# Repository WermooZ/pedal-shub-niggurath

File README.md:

# pedal-shub-niggurath

<br />This work is licensed under a <a rel="license" href="http://creativecommons.org/licenses/by-nc-sa/4.0/">Creative Commons Attribution-NonCommercial-ShareAlike 4.0 International License</a>.

Based on the **EQD Hoof** traced by **Kit Rae** at http://www.bigmuffpage.com/Big_Muff_Pi_versions_schematics_part4.html

Like original pedal it uses 2 germanium transistors on Q2 and Q3 however Q1 is changed to MSPA18 for bigger gain and has blend circuit.  

Thread on freestompboxes: https://www.freestompboxes.org/viewtopic.php?t=32611

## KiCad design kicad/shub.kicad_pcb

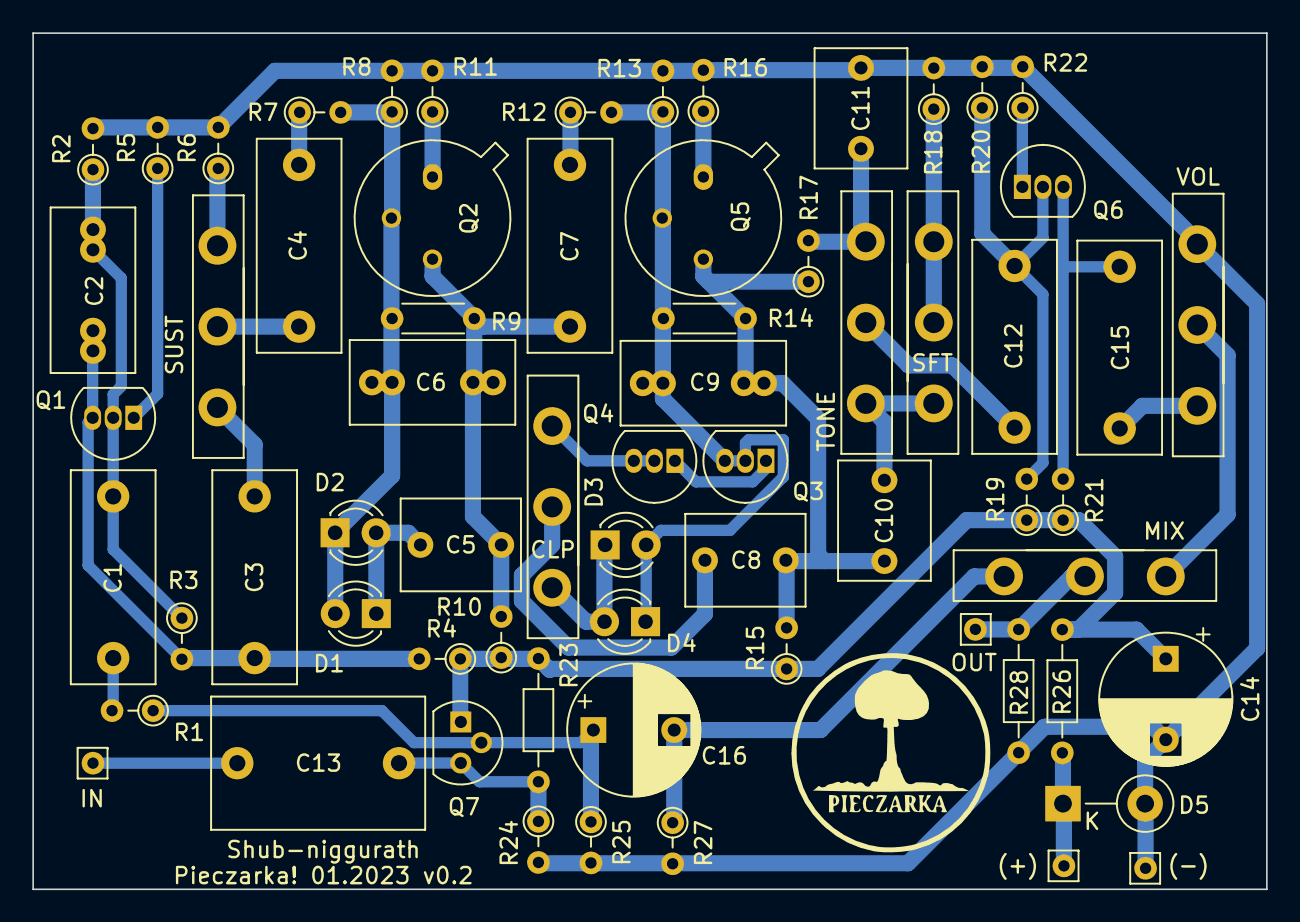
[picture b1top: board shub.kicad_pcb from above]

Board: 2 copper layers, 76.3 x 52.9 mm, 66 parts (0 on the bottom side), 37 nets.

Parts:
C1, C3, C4, C7, C12, C15: 100n; C_Rect_L13.0mm_W5.0mm_P10.00mm_FKS3_FKP3_MKS4
C2, C6, C9: 470p; C_Rect_L10.0mm_W5.0mm_P5.00mm_P7.50mm
C5: 47n; C_Rect_L7.2mm_W5.5mm_P5.00mm_FKS2_FKP2_MKS2_MKP2
C8: 22n; C_Rect_L7.2mm_W5.5mm_P5.00mm_FKS2_FKP2_MKS2_MKP2
C10, C11: 6n8; C_Rect_L7.2mm_W5.5mm_P5.00mm_FKS2_FKP2_MKS2_MKP2
C13: 1u; C_Rect_L13.0mm_W8.0mm_P10.00mm_FKS3_FKP3_MKS4
C14: 100uF; CP_Radial_D8.0mm_P5.00mm
C16: 10u; CP_Radial_D8.0mm_P5.00mm
D1, D2, D3, D4: LED; LED_D3.0mm
D5: 1N4001; D_DO-41_SOD81_P5.08mm_Vertical_KathodeUp
J1, J2, J3, J4: Conn_01x01; Pin_D0.7mm_L6.5mm_W1.8mm_FlatFork
Q1: MPSA18; TO-92_Inline
Q2, Q5: 2N1308; TO-5-3
Q3, Q4: 2N7000; TO-92_Inline
Q6: 2N3904; TO-92_Inline
Q7: Q_NJFET_DSG; TO-92L
R1, R17: 39k; R_Axial_DIN0204_L3.6mm_D1.6mm_P2.54mm_Vertical
R2, R8, R13, R20, R27: 100k; R_Axial_DIN0204_L3.6mm_D1.6mm_P2.54mm_Vertical
R3: 470k; R_Axial_DIN0204_L3.6mm_D1.6mm_P2.54mm_Vertical
R4, R10, R15: 15k; R_Axial_DIN0204_L3.6mm_D1.6mm_P2.54mm_Vertical
R5: 390R; R_Axial_DIN0204_L3.6mm_D1.6mm_P2.54mm_Vertical
R6, R18, R22: 2k2; R_Axial_DIN0204_L3.6mm_D1.6mm_P2.54mm_Vertical
R7, R12: 8k2; R_Axial_DIN0204_L3.6mm_D1.6mm_P2.54mm_Vertical
R9, R14: 470k; R_Axial_DIN0204_L3.6mm_D1.6mm_P5.08mm_Horizontal
R11, R16: 100R; R_Axial_DIN0204_L3.6mm_D1.6mm_P2.54mm_Vertical
R19: 390k; R_Axial_DIN0204_L3.6mm_D1.6mm_P2.54mm_Vertical
R21: 10k; R_Axial_DIN0204_L3.6mm_D1.6mm_P2.54mm_Vertical
R23: 1M; R_Axial_DIN0204_L3.6mm_D1.6mm_P7.62mm_Horizontal
R24: 1M; R_Axial_DIN0204_L3.6mm_D1.6mm_P2.54mm_Vertical
R25: 3k3; R_Axial_DIN0204_L3.6mm_D1.6mm_P2.54mm_Vertical
R26: 100R; R_Axial_DIN0204_L3.6mm_D1.6mm_P7.62mm_Horizontal
R28: 100k; R_Axial_DIN0204_L3.6mm_D1.6mm_P7.62mm_Horizontal
RV1: 50k; potek2
RV2, RV4: 100k; potek2
RV3: 1M; potek2
SHIFT1: 25k; potek2
SW1: SW_SPDT; potek2

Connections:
+VDC: C14.1, Q7.1 (D), R4.1, R10.1, R15.1, R19.1, R21.1, R23.1, R26.1
GND: C11.1, C14.2, D5.2 (A), J3.1, R2.2, R5.2, R6.2, R8.2, R11.2, R13.2, R16.2, R18.2, R20.2, R22.2, R24.2, R25.2, R27.2, R28.2, RV3.3
unnamed: C1.1, R1.2
unnamed: C1.2, C2.1, Q1.2 (B), R2.1, R3.1
unnamed: C2.2, C3.1, Q1.3 (C), R3.2, R4.2
unnamed: C3.2, RV1.1
unnamed: C4.1, RV1.2
unnamed: C4.2, R7.1
unnamed: C5.1, D1.1 (K), D2.2 (A)
unnamed: C5.2, C6.2, C7.1, Q2.3 (C), R9.2, R10.2
unnamed: C6.1, D1.2 (A), D2.1 (K), Q2.2 (B), R7.2, R8.1, R9.1
unnamed: C7.2, R12.1
unnamed: C8.1, SW1.2 (B)
unnamed: C9.1, D3.2 (A), D4.1 (K), Q3.2 (G), Q3.3 (D), Q5.2 (B), R12.2, R13.1, R14.1
unnamed: C10.1, RV2.1, SHIFT1.3
unnamed: C8.2, C9.2, C10.2, Q5.3 (C), R14.2, R15.2, R17.1
unnamed: C11.2, R17.2, RV2.3
unnamed: C12.1, RV2.2
unnamed: C12.2, Q6.2 (B), R19.2, R20.1
unnamed: C13.1, J1.1
unnamed: C13.2, Q7.3 (G), R23.2, R24.1
unnamed: C15.1, Q6.3 (C), R21.2
unnamed: C15.2, RV3.1
unnamed: C16.1, Q7.2 (S), R1.1, R25.1
unnamed: C16.2, R27.1, RV4.3
unnamed: D3.1 (K), D4.2 (A), SW1.1 (A)
unnamed: D5.1 (K), J2.1, R26.2
unnamed: J4.1, R28.1, RV4.2
unnamed: Q1.1 (E), R5.1
unnamed: Q2.1 (E), R11.1
unnamed: Q3.1 (S), Q4.1 (S)
unnamed: Q4.2 (G), Q4.3 (D), SW1.3 (C)
unnamed: Q5.1 (E), R16.1
unnamed: Q6.1 (E), R22.1
unnamed: R6.1, RV1.3
unnamed: R18.1, SHIFT1.1, SHIFT1.2
unnamed: RV3.2, RV4.1

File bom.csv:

Source:,,,,,,
Date:,"sob, 28 sty 2023, 21:32:28",,,,,
Tool:,Eeschema (6.0.10),,,,,
Generator:,/usr/share/kicad/plugins/bom_csv_grouped_by_value_with_fp.py,,,,,
Component Count:,66,,,,,
Ref,Qnty,Value,Cmp name,Footprint,Description,Vendor
"C1, C3, C4, C7, C12, C15, ",6,100n,C,Capacitor_THT:C_Rect_L13.0mm_W5.0mm_P10.00mm_FKS3_FKP3_MKS4,Unpolarized capacitor,
"C2, C6, C9, ",3,470p,C,Capacitor_THT:C_Rect_L10.0mm_W5.0mm_P5.00mm_P7.50mm,Unpolarized capacitor,
"C5, ",1,47n,C,Capacitor_THT:C_Rect_L7.2mm_W5.5mm_P5.00mm_FKS2_FKP2_MKS2_MKP2,Unpolarized capacitor,
"C8, ",1,22n,C,Capacitor_THT:C_Rect_L7.2mm_W5.5mm_P5.00mm_FKS2_FKP2_MKS2_MKP2,Unpolarized capacitor,
"C10, C11, ",2,6n8,C,Capacitor_THT:C_Rect_L7.2mm_W5.5mm_P5.00mm_FKS2_FKP2_MKS2_MKP2,Unpolarized capacitor,
"C13, ",1,1u,C,Capacitor_THT:C_Rect_L13.0mm_W8.0mm_P10.00mm_FKS3_FKP3_MKS4,Unpolarized capacitor,
"C14, ",1,100uF,C_Polarized,Capacitor_THT:CP_Radial_D8.0mm_P5.00mm,Polarized capacitor,
"C16, ",1,10u,C,Capacitor_THT:CP_Radial_D8.0mm_P5.00mm,Unpolarized capacitor,
"D1, D2, D3, D4, ",4,LED,LED,LED_THT:LED_D3.0mm,Light emitting diode,
"D5, ",1,1N4001,1N4001,Diode_THT:D_DO-41_SOD81_P5.08mm_Vertical_KathodeUp,"50V 1A General Purpose Rectifier Diode, DO-41",
"J1, J2, J3, J4, ",4,Conn_01x01,Conn_01x01,Connector_Pin:Pin_D0.7mm_L6.5mm_W1.8mm_FlatFork,"Generic connector, single row, 01x01, script generated (kicad-library-utils/schlib/autogen/connector/)",
"Q1, ",1,MPSA18,MPSA42,Package_TO_SOT_THT:TO-92_Inline,"0.5A Ic, 300V Vce, NPN High Voltage Transistor, TO-92",
"Q2, Q5, ",2,2N1308,2N2219,Package_TO_SOT_THT:TO-5-3,"800mA Ic, 50V Vce, NPN Transistor, TO-39",
"Q3, Q4, ",2,2N7000,2N7000,Package_TO_SOT_THT:TO-92_Inline,"0.2A Id, 200V Vds, N-Channel MOSFET, 2.6V Logic Level, TO-92",
"Q6, ",1,2N3904,2N3904,Package_TO_SOT_THT:TO-92_Inline,"0.2A Ic, 40V Vce, Small Signal NPN Transistor, TO-92",
"Q7, ",1,Q_NJFET_DSG,Q_NJFET_DSG,Package_TO_SOT_THT:TO-92L,"N-JFET transistor, drain/source/gate",
"R1, R17, ",2,39k,R,Resistor_THT:R_Axial_DIN0204_L3.6mm_D1.6mm_P2.54mm_Vertical,Resistor,
"R2, R8, R13, R20, R27, ",5,100k,R,Resistor_THT:R_Axial_DIN0204_L3.6mm_D1.6mm_P2.54mm_Vertical,Resistor,
"R3, ",1,470k,R,Resistor_THT:R_Axial_DIN0204_L3.6mm_D1.6mm_P2.54mm_Vertical,Resistor,
"R4, R10, R15, ",3,15k,R,Resistor_THT:R_Axial_DIN0204_L3.6mm_D1.6mm_P2.54mm_Vertical,Resistor,
"R5, ",1,390R,R,Resistor_THT:R_Axial_DIN0204_L3.6mm_D1.6mm_P2.54mm_Vertical,Resistor,
"R6, R18, R22, ",3,2k2,R,Resistor_THT:R_Axial_DIN0204_L3.6mm_D1.6mm_P2.54mm_Vertical,Resistor,
"R7, R12, ",2,8k2,R,Resistor_THT:R_Axial_DIN0204_L3.6mm_D1.6mm_P2.54mm_Vertical,Resistor,
"R9, R14, ",2,470k,R,Resistor_THT:R_Axial_DIN0204_L3.6mm_D1.6mm_P5.08mm_Horizontal,Resistor,
"R11, R16, ",2,100R,R,Resistor_THT:R_Axial_DIN0204_L3.6mm_D1.6mm_P2.54mm_Vertical,Resistor,
"R19, ",1,390k,R,Resistor_THT:R_Axial_DIN0204_L3.6mm_D1.6mm_P2.54mm_Vertical,Resistor,
"R21, ",1,10k,R,Resistor_THT:R_Axial_DIN0204_L3.6mm_D1.6mm_P2.54mm_Vertical,Resistor,
"R23, ",1,1M,R,Resistor_THT:R_Axial_DIN0204_L3.6mm_D1.6mm_P7.62mm_Horizontal,Resistor,
"R24, ",1,1M,R,Resistor_THT:R_Axial_DIN0204_L3.6mm_D1.6mm_P2.54mm_Vertical,Resistor,
"R25, ",1,3k3,R,Resistor_THT:R_Axial_DIN0204_L3.6mm_D1.6mm_P2.54mm_Vertical,Resistor,
"R26, ",1,100R,R,Resistor_THT:R_Axial_DIN0204_L3.6mm_D1.6mm_P7.62mm_Horizontal,Resistor,
"R28, ",1,100k,R,Resistor_THT:R_Axial_DIN0204_L3.6mm_D1.6mm_P7.62mm_Horizontal,Resistor,
"RV1, ",1,50k,R_Potentiometer,varia:potek2,Potentiometer,
"RV2, RV4, ",2,100k,R_Potentiometer,varia:potek2,Potentiometer,
"RV3, ",1,1M,R_Potentiometer,varia:potek2,Potentiometer,
"SHIFT1, ",1,25k,R_Potentiometer,varia:potek2,Potentiometer,
"SW1, ",1,SW_SPDT,SW_SPDT,varia:potek2,"Switch, single pole double throw",

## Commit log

2023-04-19 add files
2023-05-06 Add cover designs
2023-05-07 Add Kicad files and bom
